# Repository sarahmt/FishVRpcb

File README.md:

This directory contains files for editing the FishVR PCB’s in KiCad 4.0.6

Contact contributors: 

Sarah Thompson, smt2175@columbia.edu
- working on FishVR Spring 2018

For more FishVR files and info: 
https://drive.google.com/open?id=1Ii8UJhQ7dzW9s3ATLErmy2Fkt1ruH-P6

HEAT SEAL BOARD
_______________________

The heat seal board is designed to be connected to the mux board via header pins. This allows heat seal boards to be reused and fatigued separately from the mux board. The heat seal footprint was designed to match the electrode array pattern saved in this drive under FishVR/96-channel_array_Draftsight. The pitch of the interconnect pads in the footprint is 1mm. 

_______________________

MUX BOARD
_______________________

This board accommodates 11 inputs and 99 outputs. 

Inputs:

8 inputs should come from a microcontroller used to address the electrode array (see LabVIEW+Arduino Code). 

The remaining 3 inputs are V+, GND, and Vsig. V+ has been successfully tested at 5V, but datasheets for the mux IC’s in this design are contained under FishVR/Electronics_Documentation. Vsig should be connected to the current source, or whichever signal is reserved for the selected electrode. 

Outputs:

96 electrodes are accessed by these 8 inputs. The remaining 3 ouputs access electrodes 97-99 in case it becomes useful to bias these manually. 

Overall Function:

Only one electrode may be selected at a time. 4 inputs from the microncontroller are used to select 1 of 6 electrode sectors, and the other 4 inputs from the microcontroller are used to select 1/16 electrodes within the sector. All 6 muxes controlling all 6 sectors receive identical address bits, but Vsig is only routed to one mux; therefore, the unselected sector muxes output GND on all channels. A truth table is included under FishVR/Electronics_Documentation, along with a block diagram. A full schematic is contained with all the PCB files.

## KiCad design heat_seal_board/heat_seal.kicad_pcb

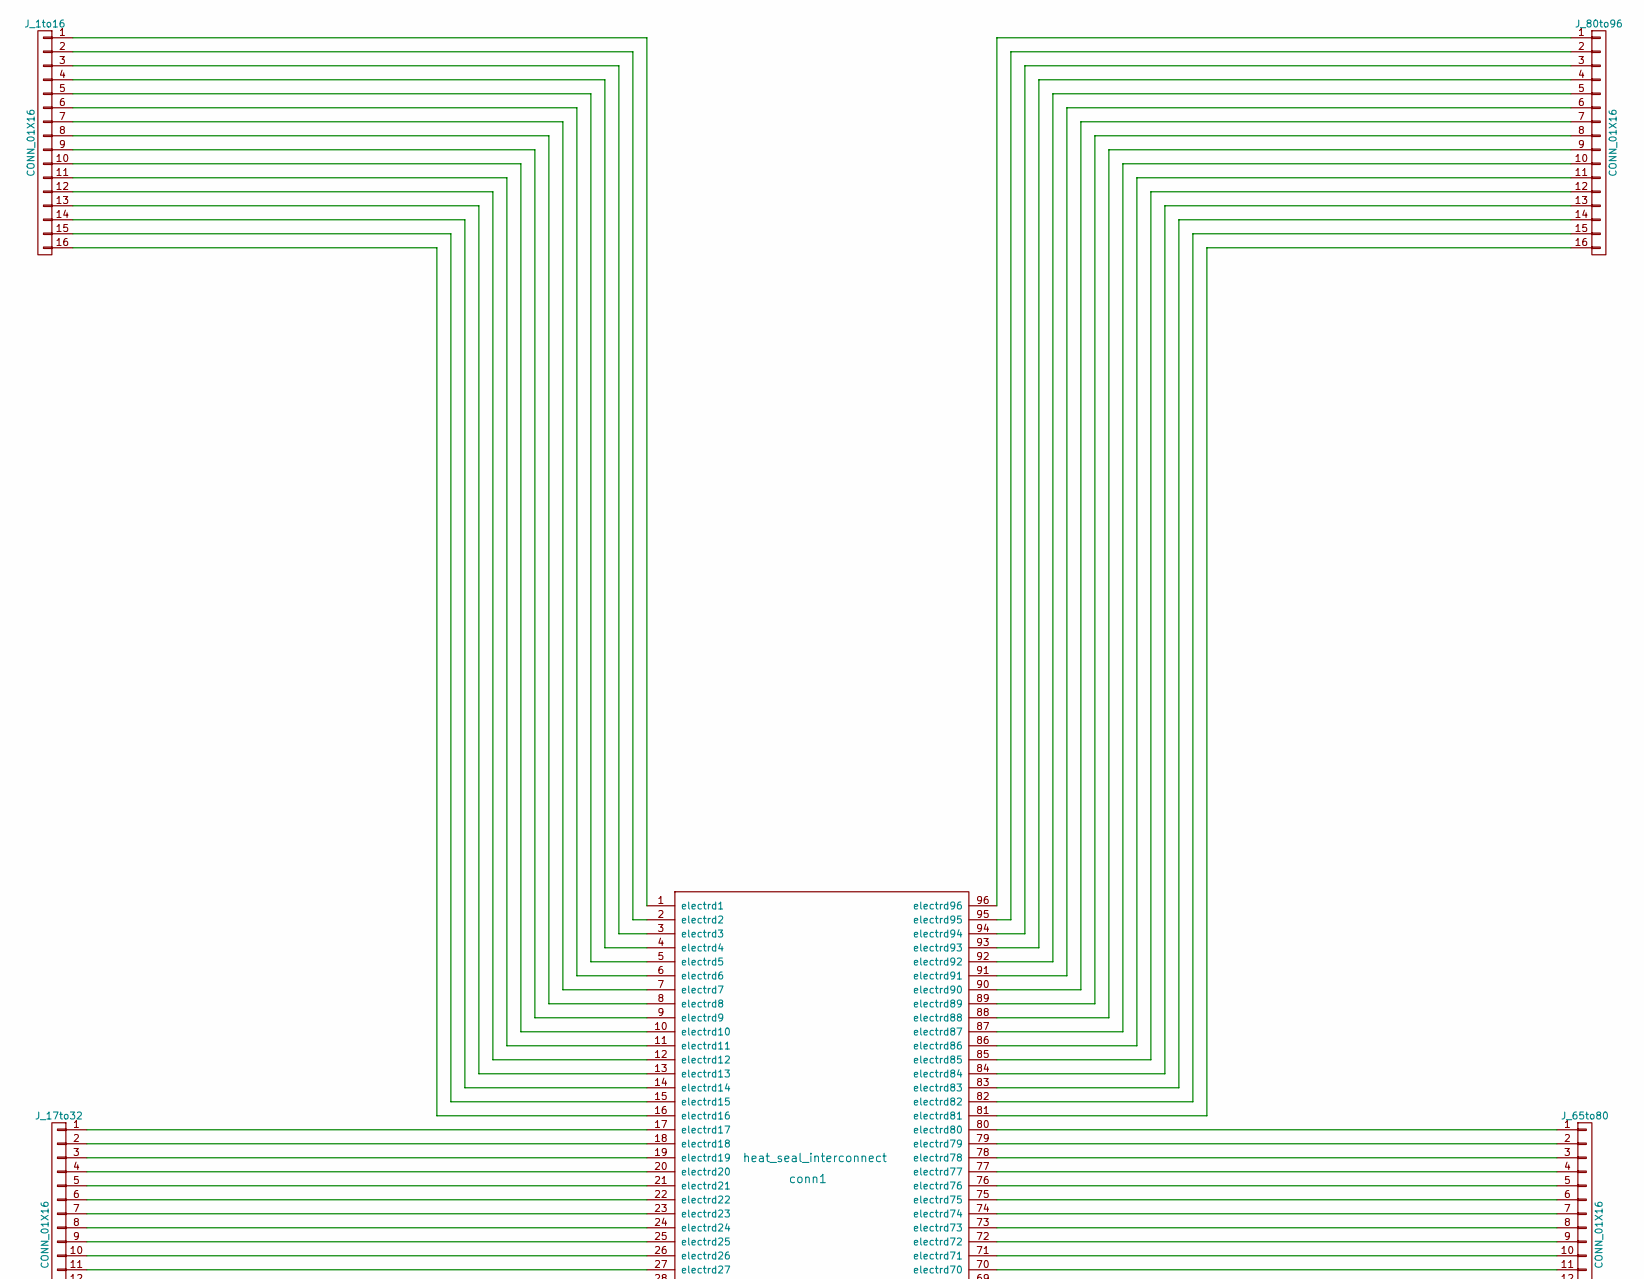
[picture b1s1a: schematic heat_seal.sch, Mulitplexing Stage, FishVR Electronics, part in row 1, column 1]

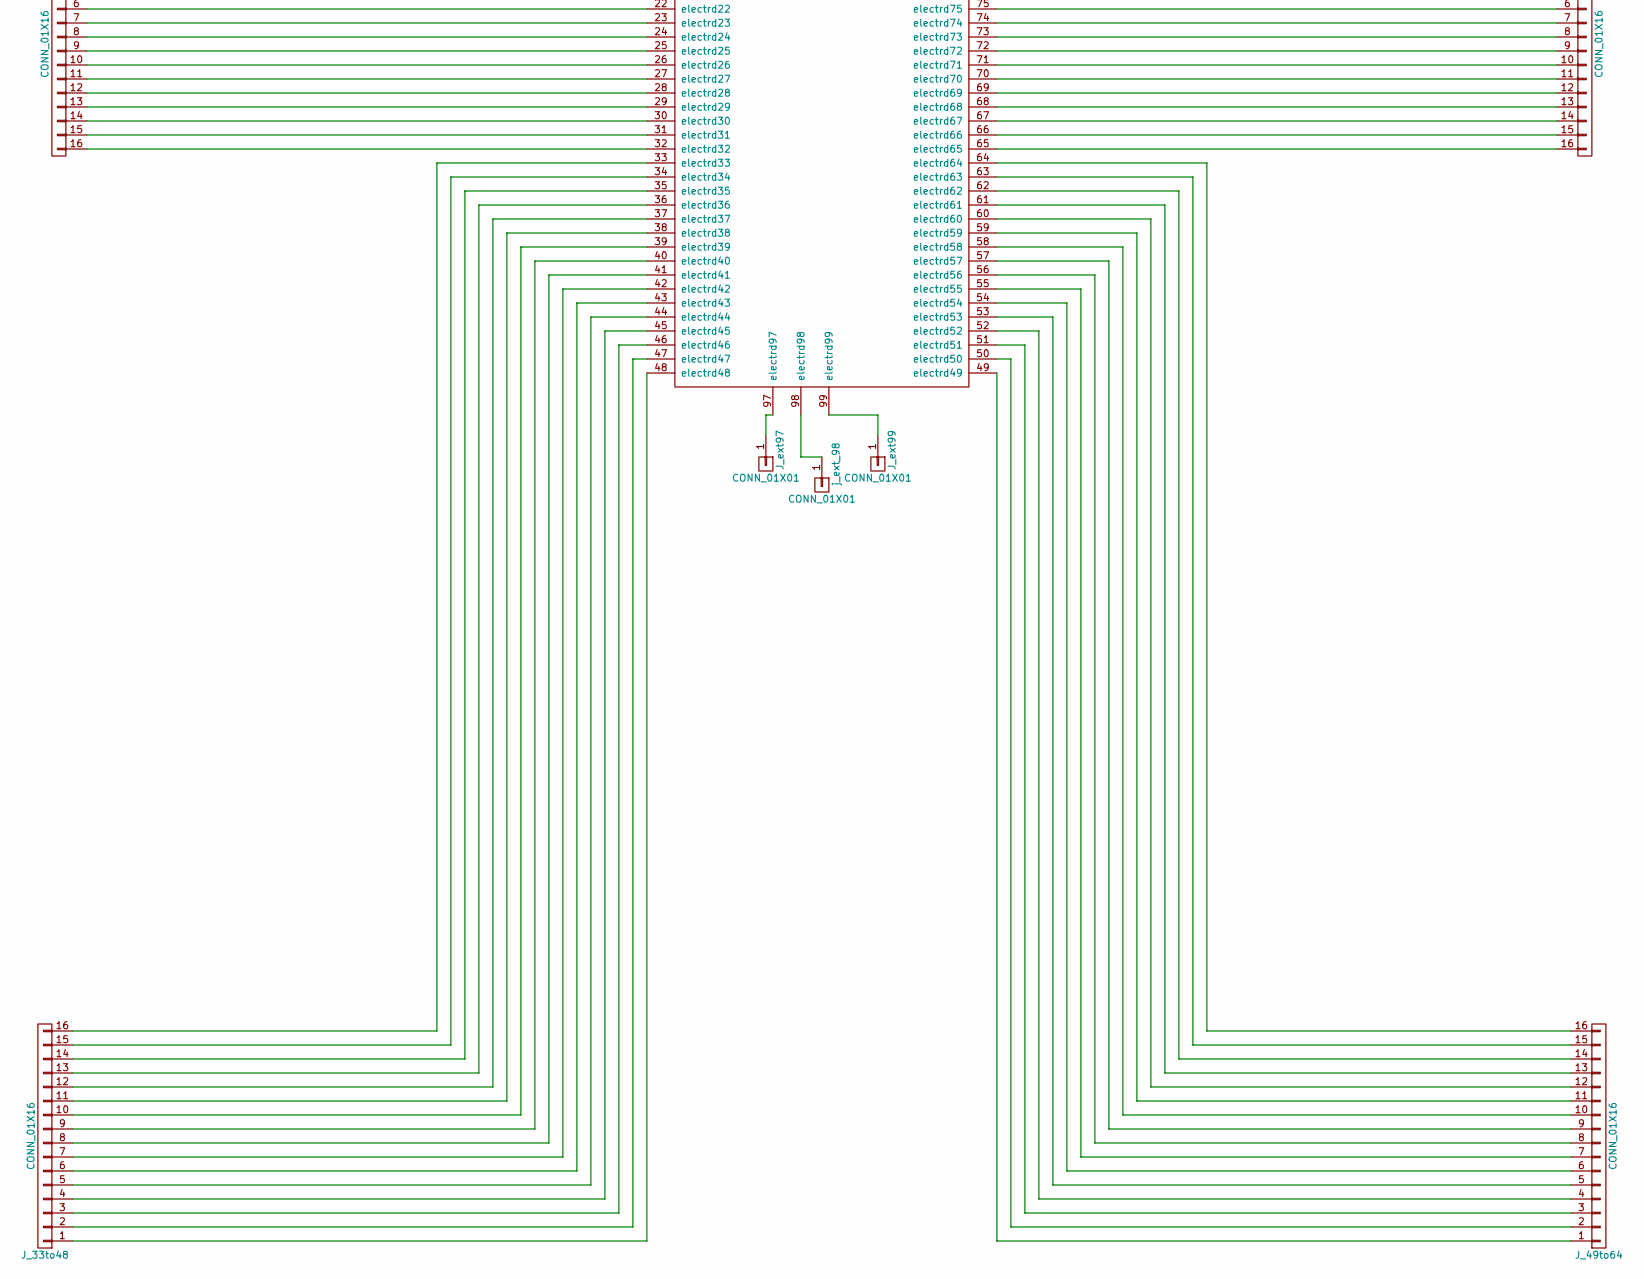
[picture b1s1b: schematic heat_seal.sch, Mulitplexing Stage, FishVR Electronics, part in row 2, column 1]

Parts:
J_1to16, J_17to32, J_33to48, J_49to64, J_65to80, J_80to96: CONN_01X16; Pin_Header_Straight_1x16_Pitch2.54mm
J_ext97, J_ext99: CONN_01X01; Pin_Header_Straight_1x01_Pitch2.54mm
conn1: heat_seal_interconnect; heat_seal_fishVR_1mmPitchx96
j_ext_98: CONN_01X01; Pin_Header_Straight_1x01_Pitch2.54mm

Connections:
unnamed: J_1to16.1, conn1.1 (electrd1)
unnamed: J_1to16.2, conn1.2 (electrd2)
unnamed: J_1to16.3, conn1.3 (electrd3)
unnamed: J_1to16.4, conn1.4 (electrd4)
unnamed: J_1to16.5, conn1.5 (electrd5)
unnamed: J_1to16.6, conn1.6 (electrd6)
unnamed: J_1to16.7, conn1.7 (electrd7)
unnamed: J_1to16.8, conn1.8 (electrd8)
unnamed: J_1to16.9, conn1.9 (electrd9)
unnamed: J_1to16.10, conn1.10 (electrd10)
unnamed: J_1to16.11, conn1.11 (electrd11)
unnamed: J_1to16.12, conn1.12 (electrd12)
unnamed: J_1to16.13, conn1.13 (electrd13)
unnamed: J_1to16.14, conn1.14 (electrd14)
unnamed: J_1to16.15, conn1.15 (electrd15)
unnamed: J_1to16.16, conn1.16 (electrd16)
unnamed: J_17to32.1, conn1.17 (electrd17)
unnamed: J_17to32.2, conn1.18 (electrd18)
unnamed: J_17to32.3, conn1.19 (electrd19)
unnamed: J_17to32.4, conn1.20 (electrd20)
unnamed: J_17to32.5, conn1.21 (electrd21)
unnamed: J_17to32.6, conn1.22 (electrd22)
unnamed: J_17to32.7, conn1.23 (electrd23)
unnamed: J_17to32.8, conn1.24 (electrd24)
unnamed: J_17to32.9, conn1.25 (electrd25)
unnamed: J_17to32.10, conn1.26 (electrd26)
unnamed: J_17to32.11, conn1.27 (electrd27)
unnamed: J_17to32.12, conn1.28 (electrd28)
unnamed: J_17to32.13, conn1.29 (electrd29)
unnamed: J_17to32.14, conn1.30 (electrd30)
unnamed: J_17to32.15, conn1.31 (electrd31)
unnamed: J_17to32.16, conn1.32 (electrd32)
unnamed: J_33to48.1, conn1.48 (electrd48)
unnamed: J_33to48.2, conn1.47 (electrd47)
unnamed: J_33to48.3, conn1.46 (electrd46)
unnamed: J_33to48.4, conn1.45 (electrd45)
unnamed: J_33to48.5, conn1.44 (electrd44)
unnamed: J_33to48.6, conn1.43 (electrd43)
unnamed: J_33to48.7, conn1.42 (electrd42)
unnamed: J_33to48.8, conn1.41 (electrd41)
unnamed: J_33to48.9, conn1.40 (electrd40)
unnamed: J_33to48.10, conn1.39 (electrd39)
unnamed: J_33to48.11, conn1.38 (electrd38)
unnamed: J_33to48.12, conn1.37 (electrd37)
unnamed: J_33to48.13, conn1.36 (electrd36)
unnamed: J_33to48.14, conn1.35 (electrd35)
unnamed: J_33to48.15, conn1.34 (electrd34)
unnamed: J_33to48.16, conn1.33 (electrd33)
unnamed: J_49to64.1, conn1.49 (electrd49)
unnamed: J_49to64.2, conn1.50 (electrd50)
unnamed: J_49to64.3, conn1.51 (electrd51)
unnamed: J_49to64.4, conn1.52 (electrd52)
unnamed: J_49to64.5, conn1.53 (electrd53)
unnamed: J_49to64.6, conn1.54 (electrd54)
unnamed: J_49to64.7, conn1.55 (electrd55)
unnamed: J_49to64.8, conn1.56 (electrd56)
unnamed: J_49to64.9, conn1.57 (electrd57)
unnamed: J_49to64.10, conn1.58 (electrd58)
unnamed: J_49to64.11, conn1.59 (electrd59)
unnamed: J_49to64.12, conn1.60 (electrd60)
unnamed: J_49to64.13, conn1.61 (electrd61)
unnamed: J_49to64.14, conn1.62 (electrd62)
unnamed: J_49to64.15, conn1.63 (electrd63)
unnamed: J_49to64.16, conn1.64 (electrd64)
unnamed: J_65to80.1, conn1.80 (electrd80)
unnamed: J_65to80.2, conn1.79 (electrd79)
unnamed: J_65to80.3, conn1.78 (electrd78)
unnamed: J_65to80.4, conn1.77 (electrd77)
unnamed: J_65to80.5, conn1.76 (electrd76)
unnamed: J_65to80.6, conn1.75 (electrd75)
unnamed: J_65to80.7, conn1.74 (electrd74)
unnamed: J_65to80.8, conn1.73 (electrd73)
unnamed: J_65to80.9, conn1.72 (electrd72)
unnamed: J_65to80.10, conn1.71 (electrd71)
unnamed: J_65to80.11, conn1.70 (electrd70)
unnamed: J_65to80.12, conn1.69 (electrd69)
unnamed: J_65to80.13, conn1.68 (electrd68)
unnamed: J_65to80.14, conn1.67 (electrd67)
unnamed: J_65to80.15, conn1.66 (electrd66)
unnamed: J_65to80.16, conn1.65 (electrd65)
unnamed: J_80to96.1, conn1.96 (electrd96)
unnamed: J_80to96.2, conn1.95 (electrd95)
unnamed: J_80to96.3, conn1.94 (electrd94)
unnamed: J_80to96.4, conn1.93 (electrd93)
unnamed: J_80to96.5, conn1.92 (electrd92)
unnamed: J_80to96.6, conn1.91 (electrd91)
unnamed: J_80to96.7, conn1.90 (electrd90)
unnamed: J_80to96.8, conn1.89 (electrd89)
unnamed: J_80to96.9, conn1.88 (electrd88)
unnamed: J_80to96.10, conn1.87 (electrd87)
unnamed: J_80to96.11, conn1.86 (electrd86)
unnamed: J_80to96.12, conn1.85 (electrd85)
unnamed: J_80to96.13, conn1.84 (electrd84)
unnamed: J_80to96.14, conn1.83 (electrd83)
unnamed: J_80to96.15, conn1.82 (electrd82)
unnamed: J_80to96.16, conn1.81 (electrd81)
unnamed: J_ext97.1, conn1.97 (electrd97)
unnamed: J_ext99.1, conn1.99 (electrd99)
unnamed: conn1.98 (electrd98), j_ext_98.1

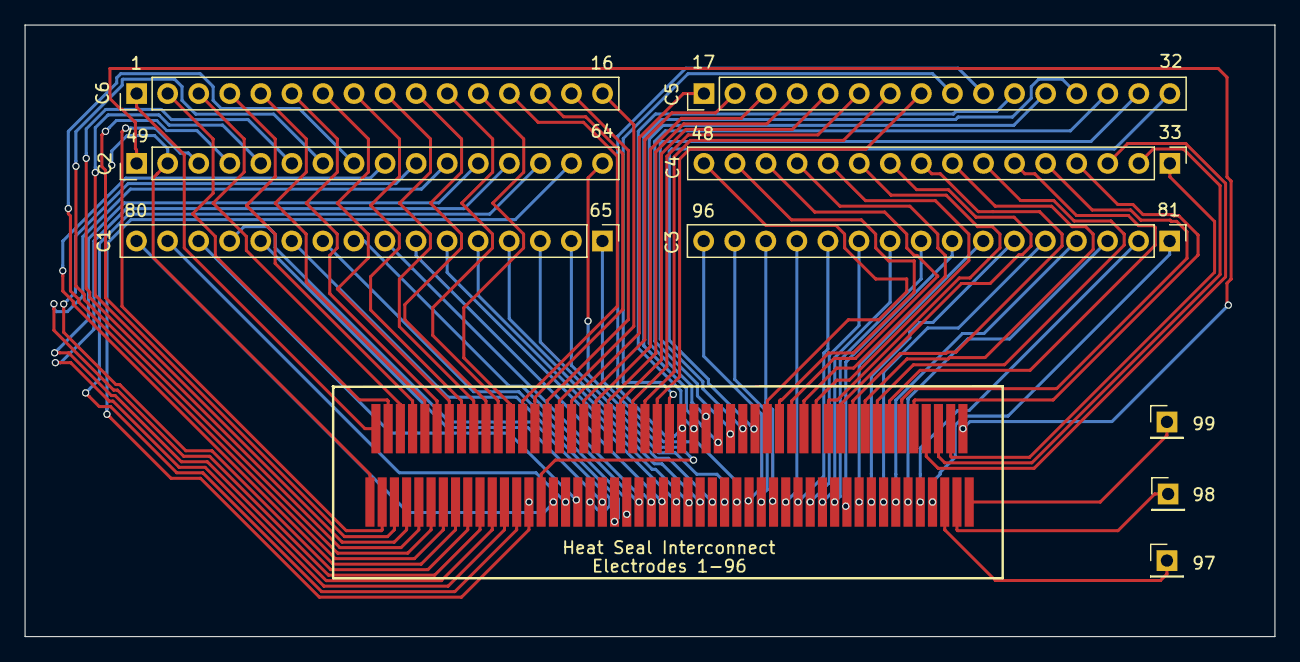
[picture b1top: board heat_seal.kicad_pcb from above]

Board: 2 copper layers, 102.2 x 50.0 mm, 10 parts (0 on the bottom side), 99 nets.

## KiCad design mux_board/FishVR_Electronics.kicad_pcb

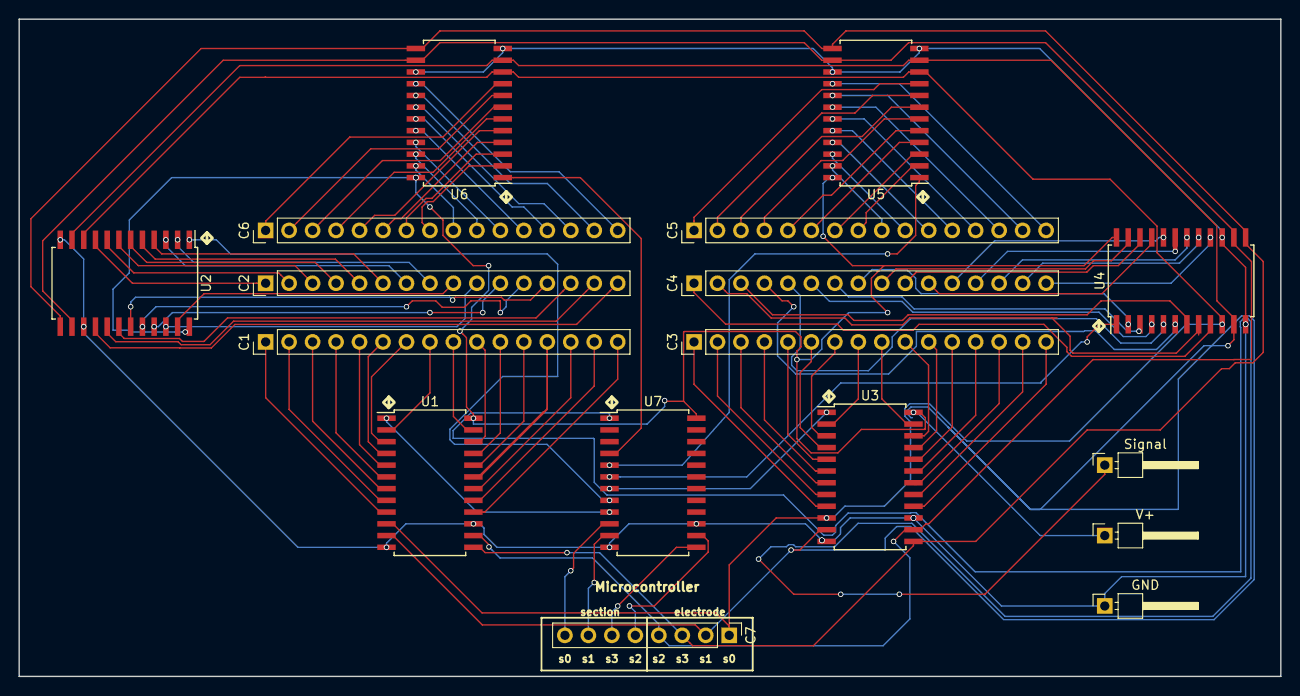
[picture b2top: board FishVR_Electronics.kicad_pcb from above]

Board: 2 copper layers, 136.5 x 71.1 mm, 17 parts (0 on the bottom side), 113 nets.

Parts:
C1, C2, C3, C4, C5, C6: CONN_01X16; Pin_Header_Straight_1x16_Pitch2.54mm
C7: Microcontroller; Pin_Header_Straight_1x08_Pitch2.54mm
GND: GND; Pin_Header_Angled_1x01_Pitch2.54mm
Signal: Vsig; Pin_Header_Angled_1x01_Pitch2.54mm
U1, U2, U3, U4, U5, U6, U7: CD74HC4067; SOIC-24W_7.5x15.4mm_Pitch1.27mm
V+: Vcc; Pin_Header_Angled_1x01_Pitch2.54mm

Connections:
+5V: U1.24, U2.24, U3.24, U4.24, U5.24, U6.24, U7.24, V+.1
GND: GND.1, U1.12, U1.15, U2.12, U2.15, U3.12, U3.15, U4.12, U4.15, U5.12, U5.15, U6.12, U6.15, U7.12, U7.15
unnamed: C1.1, U1.9
unnamed: C1.2, U1.8
unnamed: C1.3, U1.7
unnamed: C1.4, U1.6
unnamed: C1.5, U1.5
unnamed: C1.6, U1.4
unnamed: C1.7, U1.3
unnamed: C1.8, U1.2
unnamed: C1.9, U1.23
unnamed: C1.10, U1.22
unnamed: C1.11, U1.21
unnamed: C1.12, U1.20
unnamed: C1.13, U1.19
unnamed: C1.14, U1.18
unnamed: C1.15, U1.17
unnamed: C1.16, U1.16
unnamed: C2.1, U2.9
unnamed: C2.2, U2.8
unnamed: C2.3, U2.7
unnamed: C2.4, U2.6
unnamed: C2.5, U2.5
unnamed: C2.6, U2.4
unnamed: C2.7, U2.3
unnamed: C2.8, U2.2
unnamed: C2.9, U2.23
unnamed: C2.10, U2.22
unnamed: C2.11, U2.21
unnamed: C2.12, U2.20
unnamed: C2.13, U2.19
unnamed: C2.14, U2.18
unnamed: C2.15, U2.17
unnamed: C2.16, U2.16
unnamed: C3.1, U3.9
unnamed: C3.2, U3.8
unnamed: C3.3, U3.7
unnamed: C3.4, U3.6
unnamed: C3.5, U3.5
unnamed: C3.6, U3.4
unnamed: C3.7, U3.3
unnamed: C3.8, U3.2
unnamed: C3.9, U3.23
unnamed: C3.10, U3.22
unnamed: C3.11, U3.21
unnamed: C3.12, U3.20
unnamed: C3.13, U3.19
unnamed: C3.14, U3.18
unnamed: C3.15, U3.17
unnamed: C3.16, U3.16
unnamed: C4.1, U4.9
unnamed: C4.2, U4.8
unnamed: C4.3, U4.7
unnamed: C4.4, U4.6
unnamed: C4.5, U4.5
unnamed: C4.6, U4.4
unnamed: C4.7, U4.3
unnamed: C4.8, U4.2
unnamed: C4.9, U4.23
unnamed: C4.10, U4.22
unnamed: C4.11, U4.21
unnamed: C4.12, U4.20
unnamed: C4.13, U4.19
unnamed: C4.14, U4.18
unnamed: C4.15, U4.17
unnamed: C4.16, U4.16
unnamed: C5.1, U5.9
unnamed: C5.2, U5.8
unnamed: C5.3, U5.7
unnamed: C5.4, U5.6
unnamed: C5.5, U5.5
unnamed: C5.6, U5.4
unnamed: C5.7, U5.3
unnamed: C5.8, U5.2
unnamed: C5.9, U5.23
unnamed: C5.10, U5.22
unnamed: C5.11, U5.21
unnamed: C5.12, U5.20
unnamed: C5.13, U5.19
unnamed: C5.14, U5.18
unnamed: C5.15, U5.17
unnamed: C5.16, U5.16
unnamed: C6.1, U6.9
unnamed: C6.2, U6.8
unnamed: C6.3, U6.7
unnamed: C6.4, U6.6
unnamed: C6.5, U6.5
unnamed: C6.6, U6.4
unnamed: C6.7, U6.3
unnamed: C6.8, U6.2
unnamed: C6.9, U6.23
unnamed: C6.10, U6.22
unnamed: C6.11, U6.21
unnamed: C6.12, U6.20
unnamed: C6.13, U6.19
unnamed: C6.14, U6.18
unnamed: C6.15, U6.17
unnamed: C6.16, U6.16
unnamed: C7.1, U1.10, U2.10, U3.10, U4.10, U5.10, U6.10
unnamed: C7.2, U1.11, U2.11, U3.11, U4.11, U5.11, U6.11
unnamed: C7.3, U1.13, U2.13, U3.13, U4.13, U5.13, U6.13
unnamed: C7.4, U1.14, U2.14, U3.14, U4.14, U5.14, U6.14
unnamed: C7.5, U7.14
unnamed: C7.6, U7.13
unnamed: C7.7, U7.11
unnamed: C7.8, U7.10
unnamed: U1.1, U7.9
unnamed: U2.1, U7.8
unnamed: U3.1, U7.7
unnamed: U4.1, U7.6
unnamed: U5.1, U7.5
unnamed: U6.1, U7.4
Vsig: Signal.1, U7.1

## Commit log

2018-04-10 rough schematic and PCB for muxing stage
2018-04-10 replace rtf readme w/ md readme
2018-04-10 Add files via upload
    completed board with traces
    still need to add power and ground planes
2018-04-10 FishVR_Electronics.kicad_pcb
    completed board with traces
    still have to add power and ground planes
2018-04-18 finished traces and completed DRC. Ground/ power planes were not effective, so used traces instead.
2018-04-18 created gerber and drill files
2018-04-18 compressed Gerber/ to GTB.zip
2018-04-18 consolidated drill/ and gerber/
2018-04-18 consolidated drill/ gerber/
2018-04-18 consolidating drill/ gerber/
2018-04-28 added heatseal board (schematic, pcb, gerbers). These files contain designs that have been ordered in PCB minions as of Friday night 4-27-18
2018-04-28 cleaned up directory
2018-05-31 added truth table for muxing stage
2018-05-31 added copy of TI mux datasheet
2018-05-31 fixed notes on truth table
2018-06-01 added more notes to README
